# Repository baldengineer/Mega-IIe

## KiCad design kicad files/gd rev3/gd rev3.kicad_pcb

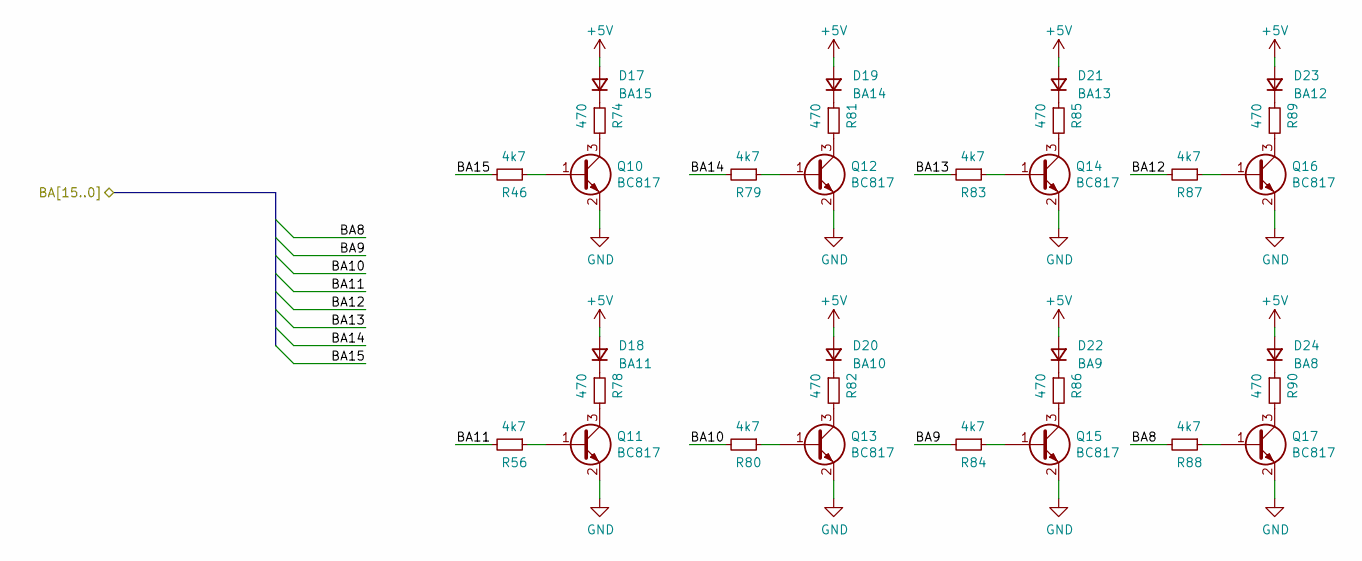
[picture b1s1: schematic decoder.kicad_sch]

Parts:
D17: BA15; LED_1206_3216Metric
D18: BA11; LED_1206_3216Metric
D19: BA14; LED_1206_3216Metric
D20: BA10; LED_1206_3216Metric
D21: BA13; LED_1206_3216Metric
D22: BA9; LED_1206_3216Metric
D23: BA12; LED_1206_3216Metric
D24: BA8; LED_1206_3216Metric
Q10, Q11, Q12, Q13, Q14, Q15, Q16, Q17: BC817; SOT-23
R46, R56, R79, R80, R83, R84, R87, R88: 4k7; R_0805_2012Metric
R74, R78, R81, R82, R85, R86, R89, R90: 470; R_0805_2012Metric

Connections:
/IWM/BA8: R88.2; also elsewhere on the board
/IWM/BA9: R84.2; also elsewhere on the board
/IWM/BA10: R80.2; also elsewhere on the board
/IWM/BA11: R56.2; also elsewhere on the board
/IWM/BA12: R87.2; also elsewhere on the board
/IWM/BA13: R83.2; also elsewhere on the board
/IWM/BA14: R79.2; also elsewhere on the board
/IWM/BA15: R46.2; also elsewhere on the board
GND: Q10.2 (E), Q11.2 (E), Q12.2 (E), Q13.2 (E), Q14.2 (E), Q15.2 (E), Q16.2 (E), Q17.2 (E); also elsewhere on the board
unnamed: D17.1 (K), R74.1
unnamed: D18.1 (K), R78.1
unnamed: D19.1 (K), R81.1
unnamed: D20.1 (K), R82.1
unnamed: D21.1 (K), R85.1
unnamed: D22.1 (K), R86.1
unnamed: D23.1 (K), R89.1
unnamed: D24.1 (K), R90.1
unnamed: Q10.1 (B), R46.1
unnamed: Q10.3 (C), R74.2
unnamed: Q11.1 (B), R56.1
unnamed: Q11.3 (C), R78.2
unnamed: Q12.1 (B), R79.1
unnamed: Q12.3 (C), R81.2
unnamed: Q13.1 (B), R80.1
unnamed: Q13.3 (C), R82.2
unnamed: Q14.1 (B), R83.1
unnamed: Q14.3 (C), R85.2
unnamed: Q15.1 (B), R84.1
unnamed: Q15.3 (C), R86.2
unnamed: Q16.1 (B), R87.1
unnamed: Q16.3 (C), R89.2
unnamed: Q17.1 (B), R88.1
unnamed: Q17.3 (C), R90.2

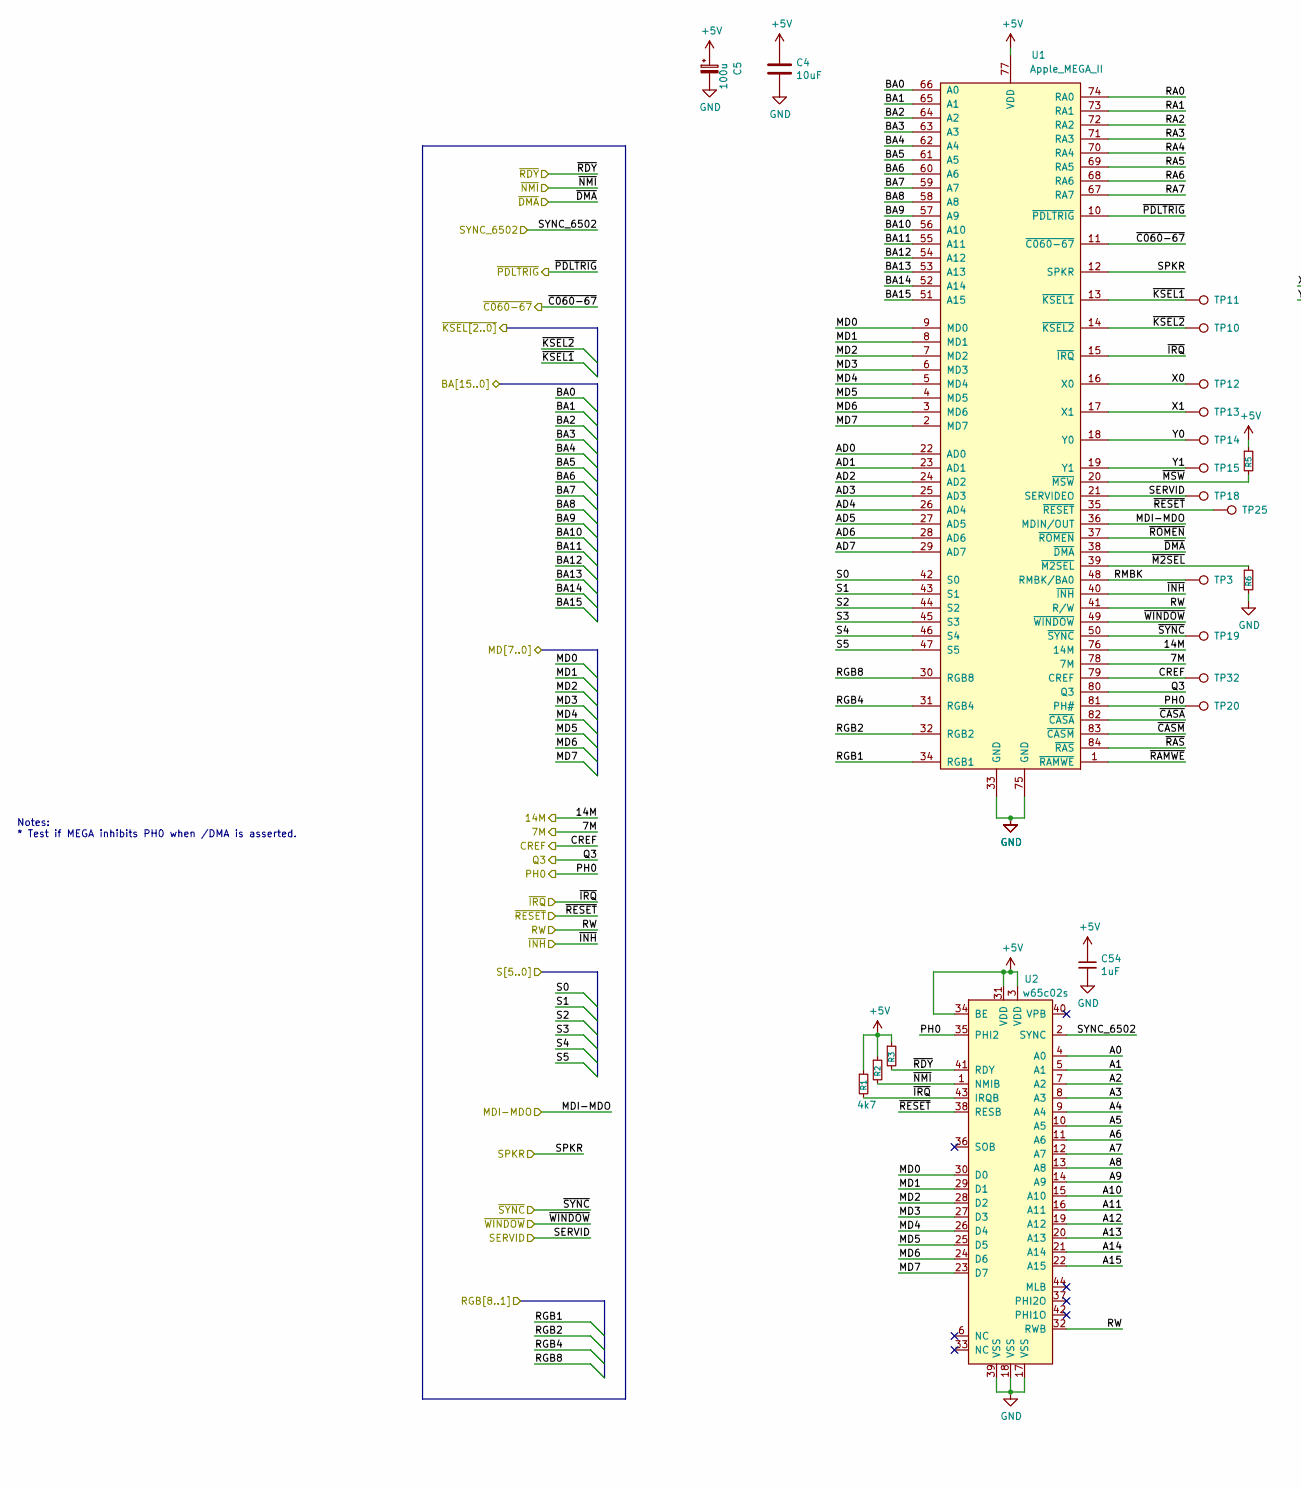
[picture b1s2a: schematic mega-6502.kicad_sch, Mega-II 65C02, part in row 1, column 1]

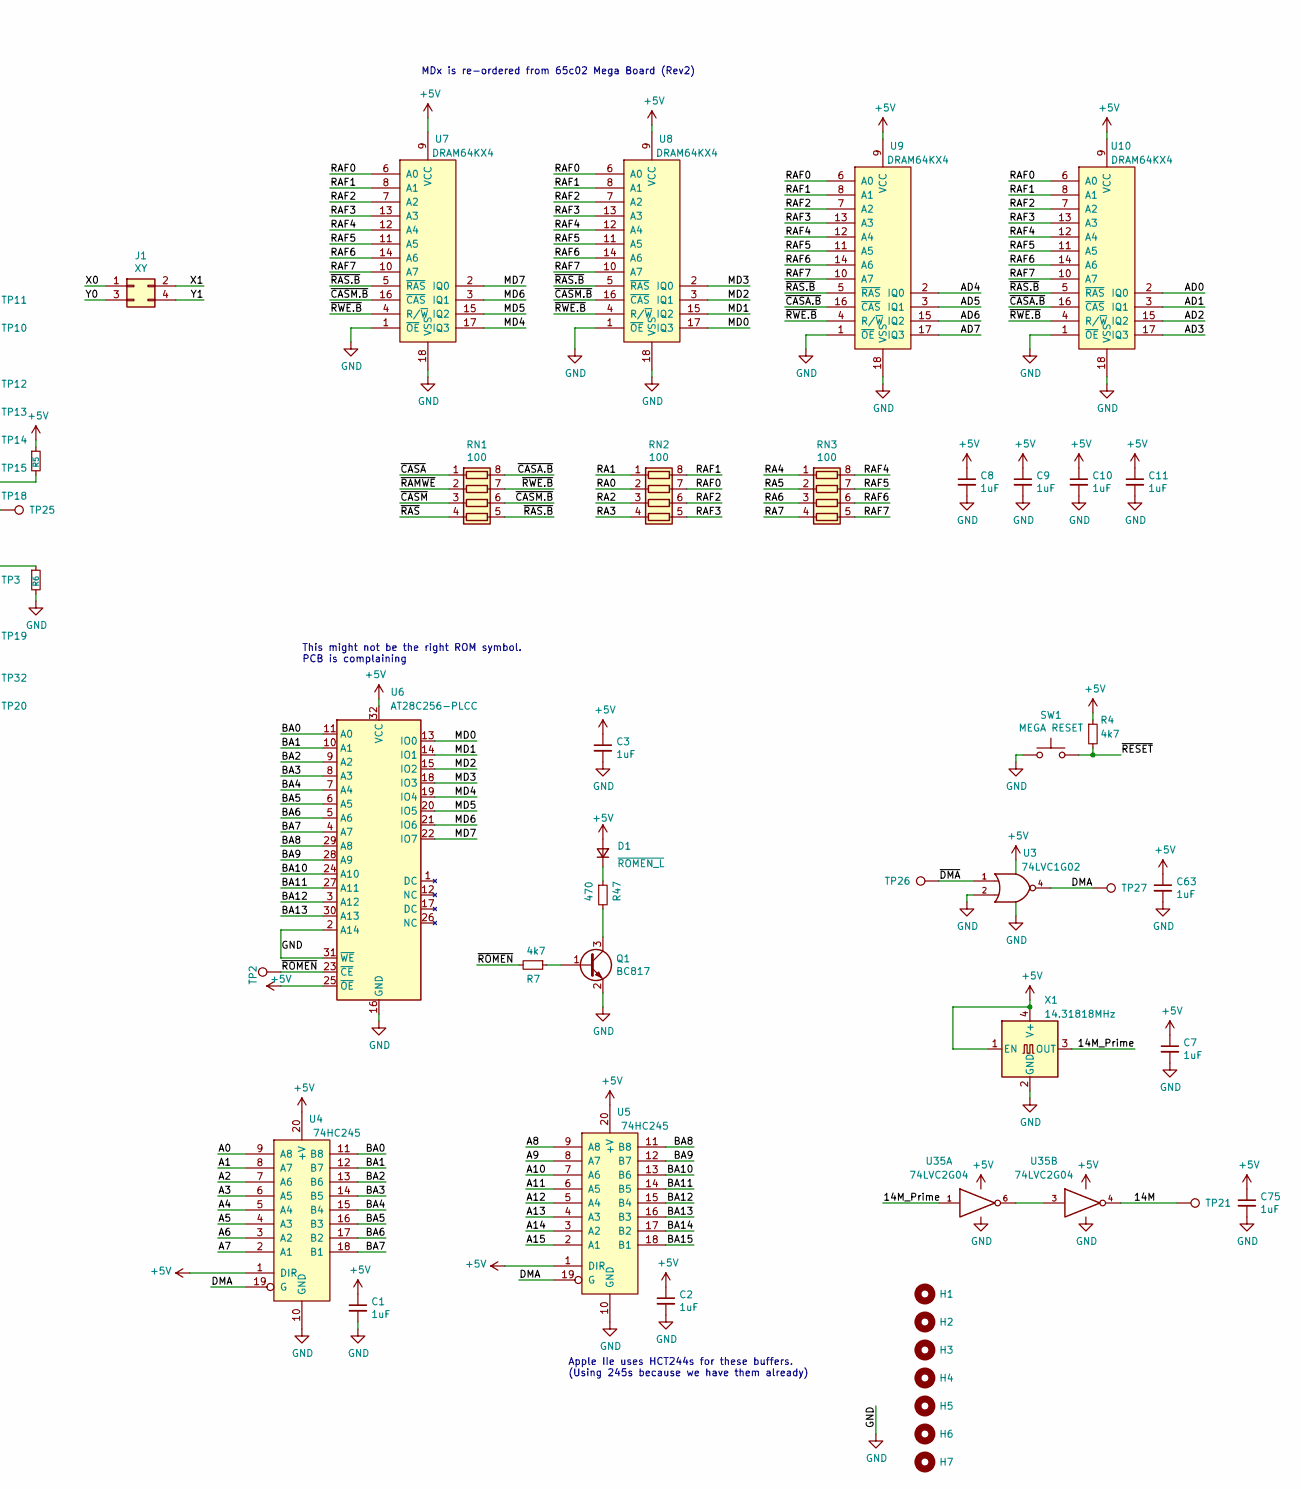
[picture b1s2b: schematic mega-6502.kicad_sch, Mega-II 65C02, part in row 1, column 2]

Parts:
C1, C2, C3, C7, C8, C9, C10, C11, C54, C63, C75: 1uF; C_0805_2012Metric
C4: 10uF; C_0805_2012Metric
C5: 100u; CP_EIA-3216-18_Kemet-A; MPN T520A107M006ATE035
D1: ~{ROMEN_L}; LED_1206_3216Metric
H1, H2, H3, H4, H5, H6, H7: MountingHole; MountingHole_2.5mm
J1: XY; PinHeader_2x02_P2.54mm_Vertical
Q1: BC817; SOT-23
R1: 4k7; R_0603_1608Metric
R2, R3: 3k3; R_0603_1608Metric
R4, R5, R6, R7: 4k7; R_0805_2012Metric
R47: 470; R_0805_2012Metric
RN1, RN2, RN3: 100; R_Array_Convex_4x0612
SW1: MEGA RESET; SW_SPST_PTS810
TP2: TestPoint_Harwin; TestPoint_Pad_D1.0mm
TP3, TP10, TP11, TP12, TP13, TP14, TP15, TP18, TP19, TP20, TP21, TP25, TP26, TP27, TP32: TestPoint; TestPoint_Pad_D1.0mm
U1: Apple_MEGA_II; PLCC-84_THT-Socket
U2: w65c02s; TQFP-44_10x10mm_P0.8mm
U3: 74LVC1G02; SOT-23-5
U4, U5: 74HC245; SO-20_5.3x12.6mm_P1.27mm
U6: AT28C256-PLCC; PLCC-32_11.4x14.0mm_P1.27mm
U7, U8, U9, U10: DRAM64KX4; DIP-18_W7.62mm_Socket_LongPads
U35: 74LVC2G04; SOT-23-6
X1: 14.31818MHz; Oscillator_SMD_EuroQuartz_XO91-4Pin_7.0x5.0mm; MPN MCSJK-6NC1-14.31818-25-B

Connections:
/Audio/SPKR: U1.12 (SPKR); also elsewhere on the board
/IWM/7M: U1.78 (7M); also elsewhere on the board
/IWM/BA0: U1.66 (A0), U4.11 (B8), U6.11 (A0); also elsewhere on the board
/IWM/BA1: U1.65 (A1), U4.12 (B7), U6.10 (A1); also elsewhere on the board
/IWM/BA2: U1.64 (A2), U4.13 (B6), U6.9 (A2); also elsewhere on the board
/IWM/BA3: U1.63 (A3), U4.14 (B5), U6.8 (A3); also elsewhere on the board
/IWM/BA4: U1.62 (A4), U4.15 (B4), U6.7 (A4); also elsewhere on the board
/IWM/BA5: U1.61 (A5), U4.16 (B3), U6.6 (A5); also elsewhere on the board
/IWM/BA6: U1.60 (A6), U4.17 (B2), U6.5 (A6); also elsewhere on the board
/IWM/BA7: U1.59 (A7), U4.18 (B1), U6.4 (A7); also elsewhere on the board
/IWM/BA8: U1.58 (A8), U5.11 (B8), U6.29 (A8); also elsewhere on the board
/IWM/BA9: U1.57 (A9), U5.12 (B7), U6.28 (A9); also elsewhere on the board
/IWM/BA10: U1.56 (A10), U5.13 (B6), U6.24 (A10); also elsewhere on the board
/IWM/BA11: U1.55 (A11), U5.14 (B5), U6.27 (A11); also elsewhere on the board
/IWM/BA12: U1.54 (A12), U5.15 (B4), U6.3 (A12); also elsewhere on the board
/IWM/BA13: U1.53 (A13), U5.16 (B3), U6.30 (A13); also elsewhere on the board
/IWM/BA14: U1.52 (A14), U5.17 (B2); also elsewhere on the board
/IWM/BA15: U1.51 (A15), U5.18 (B1); also elsewhere on the board
/IWM/MD0: U1.9 (MD0), U2.30 (D0), U6.13 (IO0), U8.17 (IQ3); also elsewhere on the board
/IWM/MD1: U1.8 (MD1), U2.29 (D1), U6.14 (IO1), U8.15 (IQ2); also elsewhere on the board
/IWM/MD2: U1.7 (MD2), U2.28 (D2), U6.15 (IO2), U8.3 (IQ1); also elsewhere on the board
/IWM/MD3: U1.6 (MD3), U2.27 (D3), U6.18 (IO3), U8.2 (IQ0); also elsewhere on the board
/IWM/MD4: U1.5 (MD4), U2.26 (D4), U6.19 (IO4), U7.17 (IQ3); also elsewhere on the board
/IWM/MD5: U1.4 (MD5), U2.25 (D5), U6.20 (IO5), U7.15 (IQ2); also elsewhere on the board
/IWM/MD6: U1.3 (MD6), U2.24 (D6), U6.21 (IO6), U7.3 (IQ1); also elsewhere on the board
/IWM/MD7: U1.2 (MD7), U2.23 (D7), U6.22 (IO7), U7.2 (IQ0); also elsewhere on the board
/IWM/Q3: U1.80 (Q3); also elsewhere on the board
/IWM/~RESET: R4.2, SW1.2, TP25.1, U1.35 (~RESET), U2.38 (RESB); also elsewhere on the board
/Slot/MDI-MDO: U1.36 (MDIN/OUT); also elsewhere on the board
/Slot/PH0: TP20.1, U1.81 (PH#), U2.35 (PHI2); also elsewhere on the board
/Slot/RW: U1.41 (R/W), U2.32 (RWB); also elsewhere on the board
/Slot/S0: U1.42 (S0); also elsewhere on the board
/Slot/S1: U1.43 (S1); also elsewhere on the board
/Slot/S2: U1.44 (S2); also elsewhere on the board
/Slot/S3: U1.45 (S3); also elsewhere on the board
/Slot/S4: U1.46 (S4); also elsewhere on the board
/Slot/S5: U1.47 (S5); also elsewhere on the board
/Slot/SYNC_6502: U2.2 (SYNC); also elsewhere on the board
/Slot/~DMA: TP26.1, U1.38 (~DMA), U3.1; also elsewhere on the board
/Slot/~INH: U1.40 (~INH); also elsewhere on the board
/Slot/~IRQ: R1.2, U1.15 (~IRQ), U2.43 (IRQB); also elsewhere on the board
/Slot/~NMI: R2.2, U2.1 (NMIB); also elsewhere on the board
/Slot/~RDY: R3.2, U2.41 (RDY); also elsewhere on the board
/game_port/~C060-67: U1.11 (~C060-67); also elsewhere on the board
/game_port/~PDLTRIG: U1.10 (~PDLTRIG); also elsewhere on the board
/mega-6502/14M: TP21.1, U1.76 (14M), U35.4; also elsewhere on the board
/mega-6502/14M_Prime: U35.1, X1.3 (OUT)
/mega-6502/A0: U2.4 (A0), U4.9 (A8)
/mega-6502/A1: U2.5 (A1), U4.8 (A7)
/mega-6502/A2: U2.7 (A2), U4.7 (A6)
/mega-6502/A3: U2.8 (A3), U4.6 (A5)
/mega-6502/A4: U2.9 (A4), U4.5 (A4)
/mega-6502/A5: U2.10 (A5), U4.4 (A3)
/mega-6502/A6: U2.11 (A6), U4.3 (A2)
/mega-6502/A7: U2.12 (A7), U4.2 (A1)
/mega-6502/A8: U2.13 (A8), U5.9 (A8)
/mega-6502/A9: U2.14 (A9), U5.8 (A7)
/mega-6502/A10: U2.15 (A10), U5.7 (A6)
/mega-6502/A11: U2.16 (A11), U5.6 (A5)
/mega-6502/A12: U2.19 (A12), U5.5 (A4)
/mega-6502/A13: U2.20 (A13), U5.4 (A3)
/mega-6502/A14: U2.21 (A14), U5.3 (A2)
/mega-6502/A15: U2.22 (A15), U5.2 (A1)
/mega-6502/AD0: U1.22 (AD0), U10.2 (IQ0)
/mega-6502/AD1: U1.23 (AD1), U10.3 (IQ1)
/mega-6502/AD2: U1.24 (AD2), U10.15 (IQ2)
/mega-6502/AD3: U1.25 (AD3), U10.17 (IQ3)
/mega-6502/AD4: U1.26 (AD4), U9.2 (IQ0)
/mega-6502/AD5: U1.27 (AD5), U9.3 (IQ1)
/mega-6502/AD6: U1.28 (AD6), U9.15 (IQ2)
/mega-6502/AD7: U1.29 (AD7), U9.17 (IQ3)
/mega-6502/CREF: TP32.1, U1.79 (CREF)
/mega-6502/DMA: TP27.1, U3.4, U4.19 (G), U5.19 (G)
/mega-6502/RA0: RN2.2 (R2.1), U1.74 (RA0)
/mega-6502/RA1: RN2.1 (R1.1), U1.73 (RA1)
/mega-6502/RA2: RN2.3 (R3.1), U1.72 (RA2)
/mega-6502/RA3: RN2.4 (R4.1), U1.71 (RA3)
/mega-6502/RA4: RN3.1 (R1.1), U1.70 (RA4)
/mega-6502/RA5: RN3.2 (R2.1), U1.69 (RA5)
/mega-6502/RA6: RN3.3 (R3.1), U1.68 (RA6)
/mega-6502/RA7: RN3.4 (R4.1), U1.67 (RA7)
/mega-6502/RAF0: RN2.7 (R2.2), U7.6 (A0), U8.6 (A0), U9.6 (A0), U10.6 (A0)
/mega-6502/RAF1: RN2.8 (R1.2), U7.8 (A1), U8.8 (A1), U9.8 (A1), U10.8 (A1)
/mega-6502/RAF2: RN2.6 (R3.2), U7.7 (A2), U8.7 (A2), U9.7 (A2), U10.7 (A2)
/mega-6502/RAF3: RN2.5 (R4.2), U7.13 (A3), U8.13 (A3), U9.13 (A3), U10.13 (A3)
/mega-6502/RAF4: RN3.8 (R1.2), U7.12 (A4), U8.12 (A4), U9.12 (A4), U10.12 (A4)
/mega-6502/RAF5: RN3.7 (R2.2), U7.11 (A5), U8.11 (A5), U9.11 (A5), U10.11 (A5)
/mega-6502/RAF6: RN3.6 (R3.2), U7.14 (A6), U8.14 (A6), U9.14 (A6), U10.14 (A6)
/mega-6502/RAF7: RN3.5 (R4.2), U7.10 (A7), U8.10 (A7), U9.10 (A7), U10.10 (A7)
/mega-6502/RGB1: U1.34 (RGB1); also elsewhere on the board
/mega-6502/RGB2: U1.32 (RGB2); also elsewhere on the board
/mega-6502/RGB4: U1.31 (RGB4); also elsewhere on the board
/mega-6502/RGB8: U1.30 (RGB8); also elsewhere on the board
/mega-6502/RMBK: TP3.1, U1.48 (RMBK/BA0)
/mega-6502/SERVID: TP18.1, U1.21 (SERVIDEO)
/mega-6502/X0: J1.1, TP12.1, U1.16 (X0)
/mega-6502/X1: J1.2, TP13.1, U1.17 (X1)
/mega-6502/Y0: J1.3, TP14.1, U1.18 (Y0)
/mega-6502/Y1: J1.4, TP15.1, U1.19 (Y1)
/mega-6502/~CASA.B: RN1.8 (R1.2), U9.16 (~CAS), U10.16 (~CAS)
/mega-6502/~CASA: RN1.1 (R1.1), U1.82 (~CASA)
/mega-6502/~CASM.B: RN1.6 (R3.2), U7.16 (~CAS), U8.16 (~CAS)
/mega-6502/~CASM: RN1.3 (R3.1), U1.83 (~CASM)
/mega-6502/~KSEL1: TP11.1, U1.13 (~KSEL1); also elsewhere on the board
/mega-6502/~KSEL2: TP10.1, U1.14 (~KSEL2); also elsewhere on the board
/mega-6502/~M2SEL: R6.1, U1.39 (~M2SEL)
/mega-6502/~MSW: R5.2, U1.20 (~MSW)
/mega-6502/~RAMWE: RN1.2 (R2.1), U1.1 (~RAMWE)
/mega-6502/~RAS.B: RN1.5 (R4.2), U7.5 (~RAS), U8.5 (~RAS), U9.5 (~RAS), U10.5 (~RAS)
/mega-6502/~RAS: RN1.4 (R4.1), U1.84 (~RAS)
/mega-6502/~ROMEN: R7.2, TP2.1, U1.37 (~ROMEN), U6.23 (~CE)
/mega-6502/~RWE.B: RN1.7 (R2.2), U7.4 (R/~W), U8.4 (R/~W), U9.4 (R/~W), U10.4 (R/~W)
/mega-6502/~SYNC: TP19.1, U1.50 (~SYNC); also elsewhere on the board
/mega-6502/~WINDOW: U1.49 (~WINDOW); also elsewhere on the board
GND: C1.2, C2.2, C3.2, C4.2, C5.2, C7.2, C8.2, C9.2, C10.2, C11.2, C54.2, C63.2, C75.2, Q1.2 (E), R6.2, SW1.1, U1.33 (GND), U1.75 (GND), U2.17 (VSS), U2.18 (VSS), U2.39 (VSS), U3.2, U3.3 (GND), U4.10 (GND), U5.10 (GND), U6.2 (A14), U6.16 (GND), U6.31 (~WE), U7.1 (~OE), U7.18 (VSS), U8.1 (~OE), U8.18 (VSS), U9.1 (~OE), U9.18 (VSS), U10.1 (~OE), U10.18 (VSS), U35.2 (GND), X1.2 (GND); also elsewhere on the board
unnamed: D1.1 (K), R47.1
unnamed: Q1.1 (B), R7.1
unnamed: Q1.3 (C), R47.2
unnamed: U35.3, U35.6

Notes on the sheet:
MDx is re-ordered from 65c02 Mega Board (Rev2)
Apple IIe uses HCT244s for these buffers. (Using 245s because we have them already)
This might not be the right ROM symbol. PCB is complaining
Notes: * Test if MEGA inhibits PH0 when /DMA is asserted.

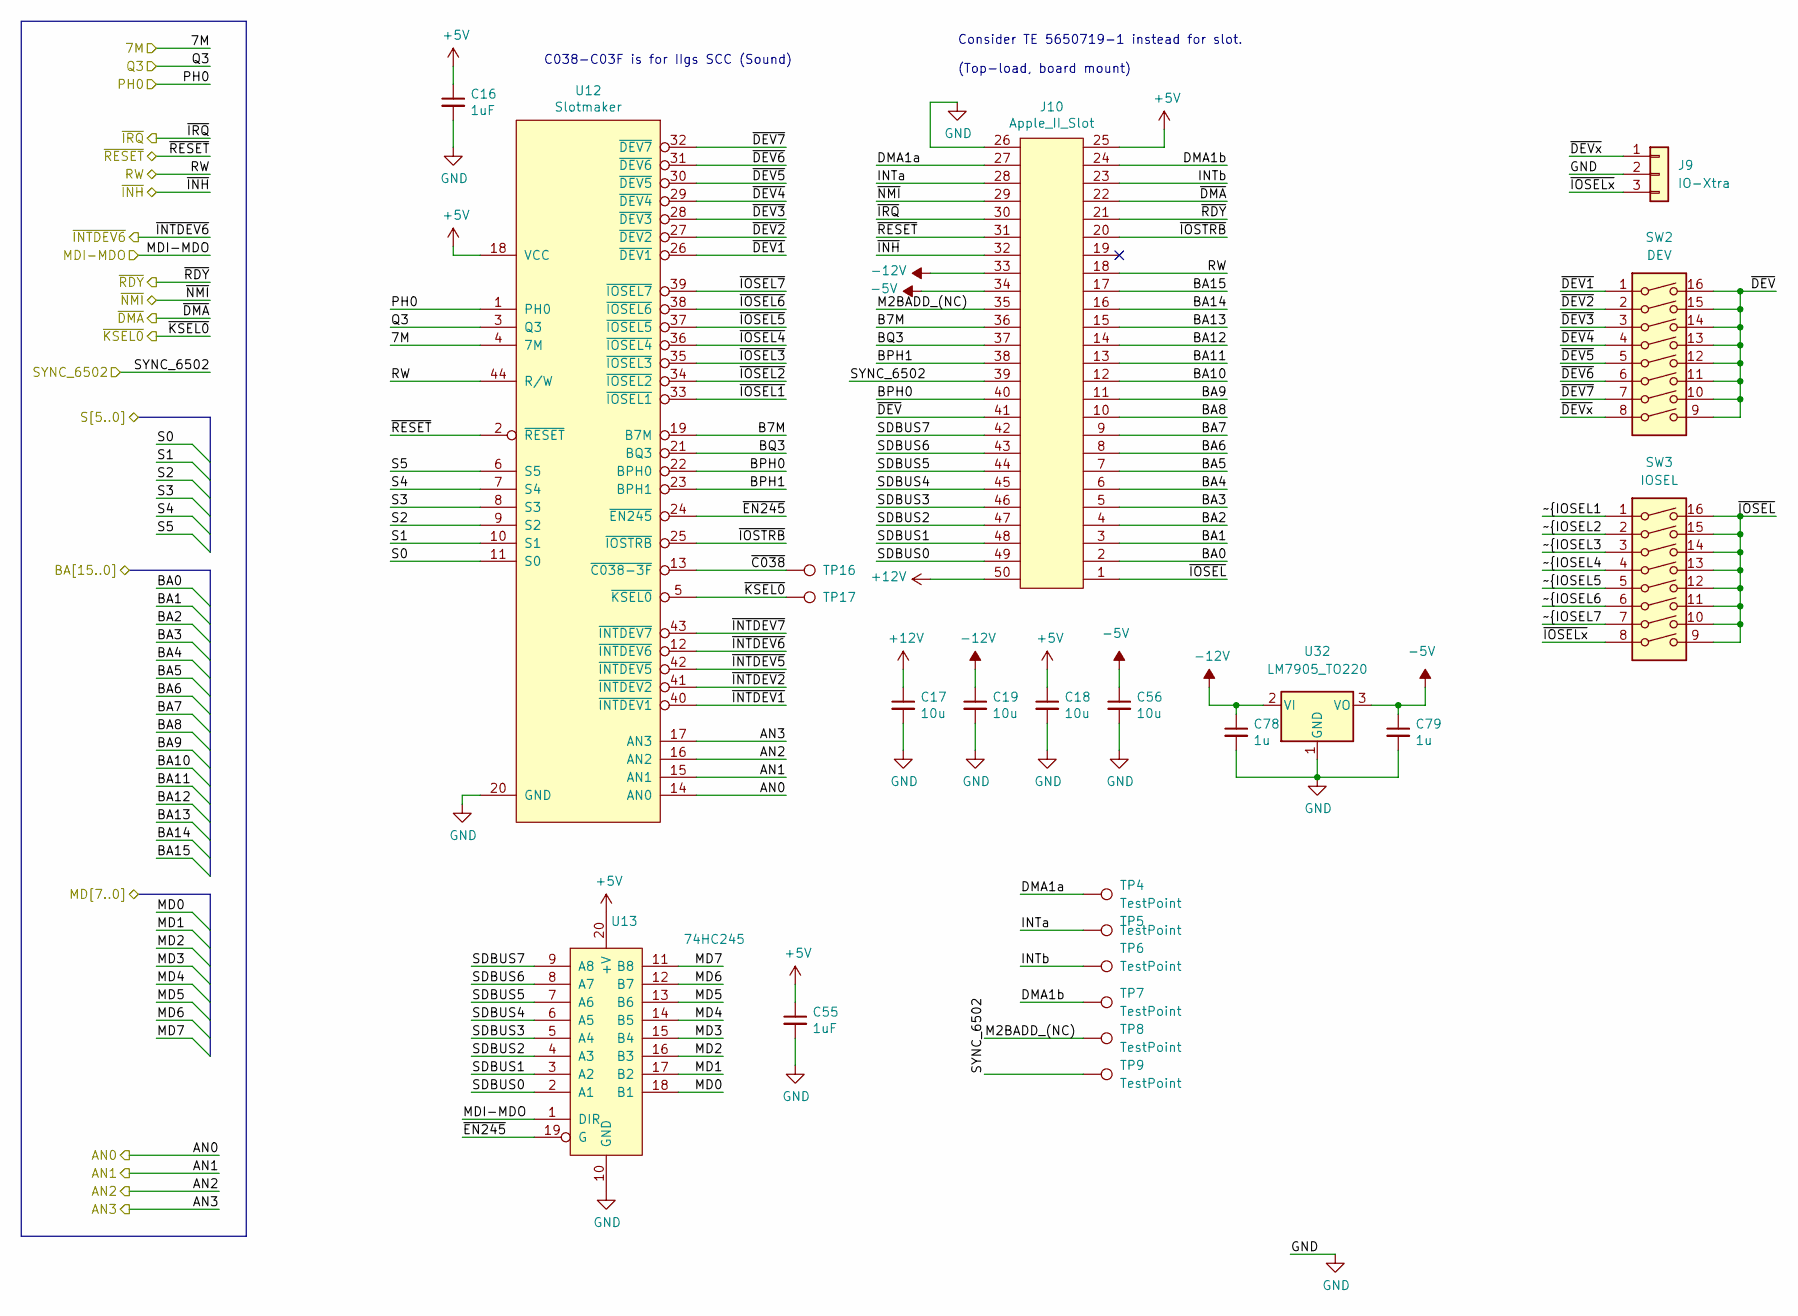
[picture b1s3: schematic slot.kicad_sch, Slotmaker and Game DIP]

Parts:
C16, C55: 1uF; C_0805_2012Metric
C17, C18, C19, C56: 10u; C_0805_2012Metric
C78, C79: 1u; C_0603_1608Metric
J9: IO-Xtra; PinHeader_1x03_P2.54mm_Vertical
J10: Apple_II_Slot; Sullins-EBC25DCWN-Edge Socket 50 pos (25x2) 0.100
SW2: DEV; SW_DIP_SPSTx08_Slide_Omron_A6H-8101_W6.15mm_P1.27mm
SW3: IOSEL; SW_DIP_SPSTx08_Slide_Omron_A6H-8101_W6.15mm_P1.27mm
TP4, TP5, TP6, TP7, TP8, TP9, TP16, TP17: TestPoint; TestPoint_Pad_D1.0mm
U12: Slotmaker; PLCC-44_THT-Socket
U13: 74HC245; SO-20_5.3x12.6mm_P1.27mm
U32: LM7905_TO220; TO-220-3_Vertical

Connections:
+12V: C17.1, J10.50; also elsewhere on the board
-5V: C56.1, C79.1, J10.34, U32.3 (VO)
-12V: C19.1, C78.1, J10.33, U32.2 (VI); also elsewhere on the board
/IWM/7M: U12.4 (7M); also elsewhere on the board
/IWM/BA0: J10.2; also elsewhere on the board
/IWM/BA1: J10.3; also elsewhere on the board
/IWM/BA2: J10.4; also elsewhere on the board
/IWM/BA3: J10.5; also elsewhere on the board
/IWM/BA4: J10.6; also elsewhere on the board
/IWM/BA5: J10.7; also elsewhere on the board
/IWM/BA6: J10.8; also elsewhere on the board
/IWM/BA7: J10.9; also elsewhere on the board
/IWM/BA8: J10.10; also elsewhere on the board
/IWM/BA9: J10.11; also elsewhere on the board
/IWM/BA10: J10.12; also elsewhere on the board
/IWM/BA11: J10.13; also elsewhere on the board
/IWM/BA12: J10.14; also elsewhere on the board
/IWM/BA13: J10.15; also elsewhere on the board
/IWM/BA14: J10.16; also elsewhere on the board
/IWM/BA15: J10.17; also elsewhere on the board
/IWM/MD0: U13.18 (B1); also elsewhere on the board
/IWM/MD1: U13.17 (B2); also elsewhere on the board
/IWM/MD2: U13.16 (B3); also elsewhere on the board
/IWM/MD3: U13.15 (B4); also elsewhere on the board
/IWM/MD4: U13.14 (B5); also elsewhere on the board
/IWM/MD5: U13.13 (B6); also elsewhere on the board
/IWM/MD6: U13.12 (B7); also elsewhere on the board
/IWM/MD7: U13.11 (B8); also elsewhere on the board
/IWM/Q3: U12.3 (Q3); also elsewhere on the board
/IWM/~INTDEV6: U12.12 (~INTDEV6); also elsewhere on the board
/IWM/~RESET: J10.31, U12.2 (~RESET); also elsewhere on the board
/Slot/AN0: U12.14 (AN0); also elsewhere on the board
/Slot/AN1: U12.15 (AN1); also elsewhere on the board
/Slot/AN2: U12.16 (AN2); also elsewhere on the board
/Slot/AN3: U12.17 (AN3); also elsewhere on the board
/Slot/B7M: J10.36, U12.19 (B7M)
/Slot/BPH0: J10.40, U12.22 (BPH0)
/Slot/BPH1: J10.38, U12.23 (BPH1)
/Slot/BQ3: J10.37, U12.21 (BQ3)
/Slot/DMA1a: J10.27, TP4.1
/Slot/DMA1b: J10.24, TP7.1
/Slot/INTa: J10.28, TP5.1
/Slot/INTb: J10.23, TP6.1
/Slot/M2BADD_(NC): J10.35, TP8.1
/Slot/MDI-MDO: U13.1 (DIR); also elsewhere on the board
/Slot/PH0: U12.1 (PH0); also elsewhere on the board
/Slot/RW: J10.18, U12.44 (R/W); also elsewhere on the board
/Slot/S0: U12.11 (S0); also elsewhere on the board
/Slot/S1: U12.10 (S1); also elsewhere on the board
/Slot/S2: U12.9 (S2); also elsewhere on the board
/Slot/S3: U12.8 (S3); also elsewhere on the board
/Slot/S4: U12.7 (S4); also elsewhere on the board
/Slot/S5: U12.6 (S5); also elsewhere on the board
/Slot/SDBUS0: J10.49, U13.2 (A1)
/Slot/SDBUS1: J10.48, U13.3 (A2)
/Slot/SDBUS2: J10.47, U13.4 (A3)
/Slot/SDBUS3: J10.46, U13.5 (A4)
/Slot/SDBUS4: J10.45, U13.6 (A5)
/Slot/SDBUS5: J10.44, U13.7 (A6)
/Slot/SDBUS6: J10.43, U13.8 (A7)
/Slot/SDBUS7: J10.42, U13.9 (A8)
/Slot/SYNC_6502: J10.39, TP9.1; also elsewhere on the board
/Slot/~C038: TP16.1, U12.13 (~C038-3F)
/Slot/~DEV1: SW2.1, U12.26 (~DEV1)
/Slot/~DEV2: SW2.2, U12.27 (~DEV2)
/Slot/~DEV3: SW2.3, U12.28 (~DEV3)
/Slot/~DEV4: SW2.4, U12.29 (~DEV4)
/Slot/~DEV5: SW2.5, U12.30 (~DEV5)
/Slot/~DEV6: SW2.6, U12.31 (~DEV6)
/Slot/~DEV7: SW2.7, U12.32 (~DEV7)
/Slot/~DEVx: J9.1, SW2.8
/Slot/~DEV: J10.41, SW2.9, SW2.10, SW2.11, SW2.12, SW2.13, SW2.14, SW2.15, SW2.16
/Slot/~DMA: J10.22; also elsewhere on the board
/Slot/~EN245: U12.24 (~EN245), U13.19 (G)
/Slot/~INH: J10.32; also elsewhere on the board
/Slot/~INTDEV1: U12.40 (~INTDEV1)
/Slot/~INTDEV2: U12.41 (~INTDEV2)
/Slot/~INTDEV5: U12.42 (~INTDEV5)
/Slot/~INTDEV7: U12.43 (~INTDEV7)
/Slot/~IOSELx: J9.3, SW3.8
/Slot/~IOSEL: J10.1, SW3.9, SW3.10, SW3.11, SW3.12, SW3.13, SW3.14, SW3.15, SW3.16
/Slot/~IOSTRB: J10.20, U12.25 (~IOSTRB)
/Slot/~IRQ: J10.30; also elsewhere on the board
/Slot/~NMI: J10.29; also elsewhere on the board
/Slot/~RDY: J10.21; also elsewhere on the board
/mega-6502/~KSEL0: TP17.1, U12.5 (~KSEL0); also elsewhere on the board
GND: C16.2, C17.2, C18.2, C19.2, C55.2, C56.2, C78.2, C79.2, J9.2, J10.26, U12.20 (GND), U13.10 (GND), U32.1 (GND); also elsewhere on the board

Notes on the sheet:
Consider TE 5650719-1 instead for slot. (Top-load, board mount)
C038-C03F is for IIgs SCC (Sound)
~{}

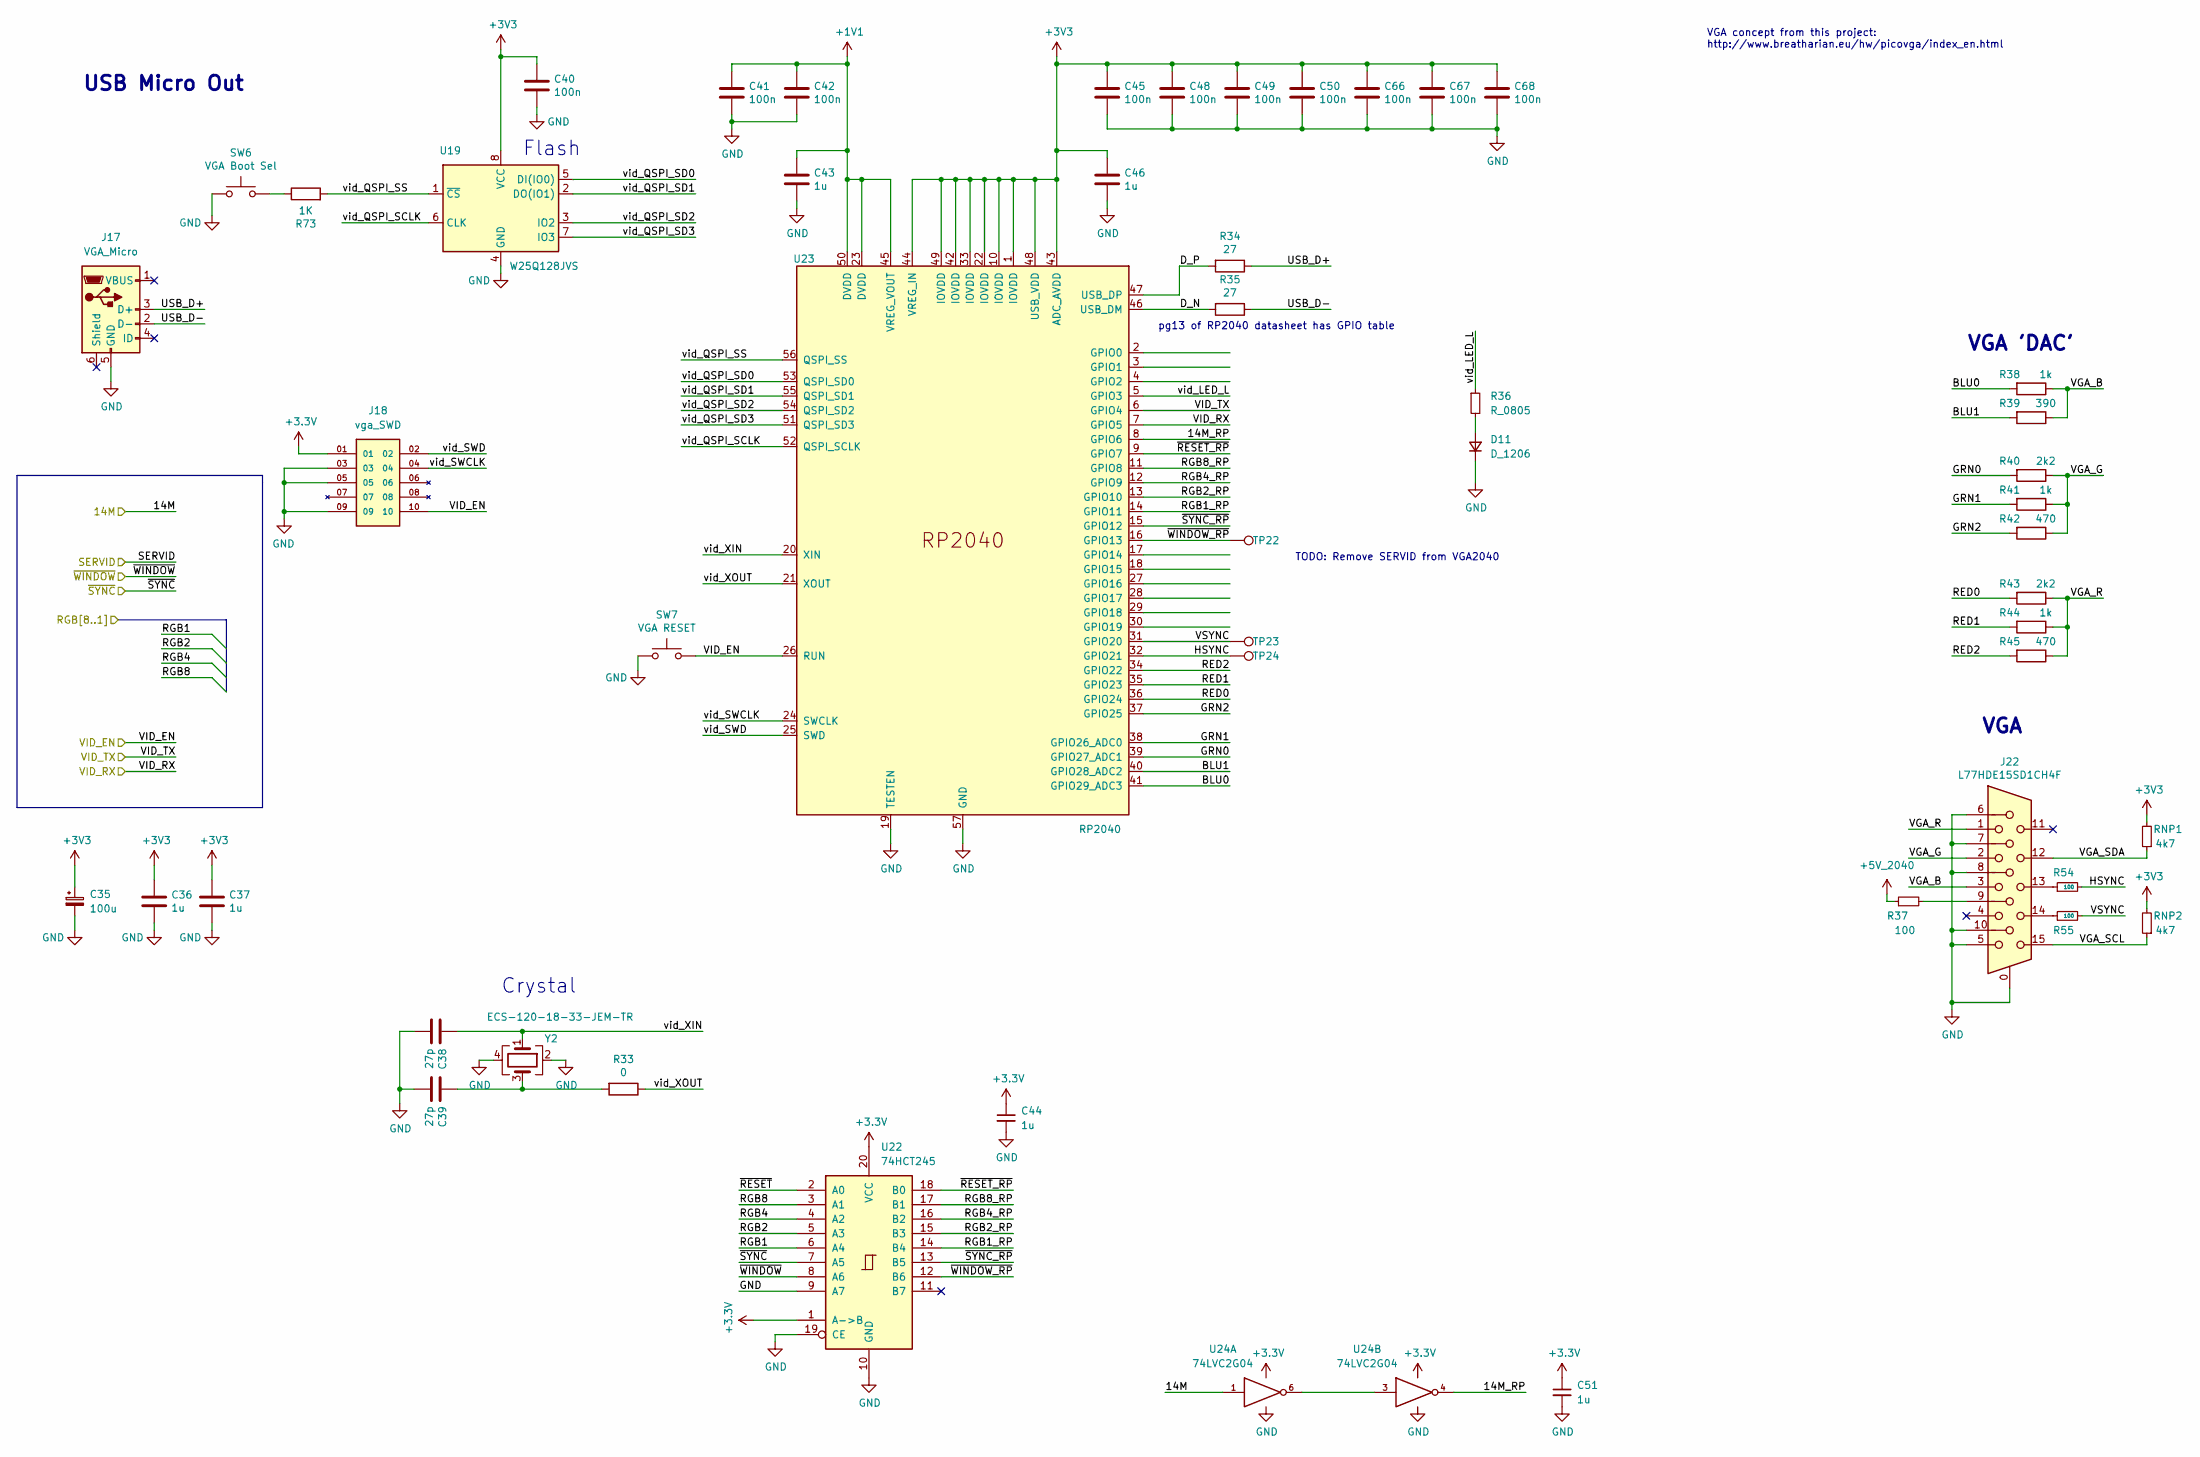
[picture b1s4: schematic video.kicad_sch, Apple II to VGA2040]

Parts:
C35: 100u; CP_EIA-3216-18_Kemet-A; MPN T520A107M006ATE035
C36, C37, C44, C51: 1u; C_0805_2012Metric
C38, C39: 27p; C_0603_1608Metric
C40: 100n; C_0805_2012Metric
C41, C42, C45, C48, C49, C50, C66, C67, C68: 100n; C_0603_1608Metric
C43, C46: 1u; C_0603_1608Metric
D11: D_1206; LED_1206_3216Metric
J17: VGA_Micro; USB_Micro-B_GCT_USB3076-30-A
J18: vga_SWD; SAMTEC_FTSH-105-XX-X-DV; PARTREV H
J22: L77HDE15SD1CH4F; DSUB-15-HD_Female_Horizontal_P2.29x1.98mm_EdgePinOffset8.35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
R33: 0; R_0603_1608Metric
R34, R35: 27; R_0603_1608Metric
R36: R_0805; R_0805_2012Metric
R37, R54, R55: 100; R_0805_2012Metric
R38, R41, R44: 1k; R_0402_1005Metric
R39: 390; R_0402_1005Metric
R40, R43: 2k2; R_0402_1005Metric
R42, R45: 470; R_0402_1005Metric
R73: 1K; R_0603_1608Metric
RNP1, RNP2: 4k7; R_0805_2012Metric
SW6: VGA Boot Sel; SW_SPST_PTS810
SW7: VGA RESET; SW_SPST_PTS810
TP22, TP23, TP24: TestPoint_Harwin; TestPoint_Pad_D1.0mm
U19: W25Q128JVS; SOIC-8_5.23x5.23mm_P1.27mm
U22: 74HCT245; SO-20_5.3x12.6mm_P1.27mm
U23: RP2040; RP2040-QFN-56
U24: 74LVC2G04; SOT-23-6
Y2: ECS-120-18-33-JEM-TR; Crystal_SMD_3225-4Pin_3.2x2.5mm

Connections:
+1V1: C41.1, C42.1, C43.1, U23.23 (DVDD), U23.45 (VREG_VOUT), U23.50 (DVDD); also elsewhere on the board
/mega-6502/14M: U24.1; also elsewhere on the board
/mega-6502/RGB1: U22.6 (A4); also elsewhere on the board
/mega-6502/RGB2: U22.5 (A3); also elsewhere on the board
/mega-6502/RGB4: U22.4 (A2); also elsewhere on the board
/mega-6502/RGB8: U22.3 (A1); also elsewhere on the board
/mega-6502/~SYNC: U22.7 (A5); also elsewhere on the board
/mega-6502/~WINDOW: U22.8 (A6); also elsewhere on the board
/rp2040-keyboard/RX_2040: U23.6 (GPIO4); also elsewhere on the board
/rp2040-keyboard/TX_2040: U23.7 (GPIO5); also elsewhere on the board
/rp2040-keyboard/VID_EN: J18.10, SW7.2, U23.26 (RUN)
/video/14M_RP: U23.8 (GPIO6), U24.4
/video/BLU0: R38.2, U23.41 (GPIO29_ADC3)
/video/BLU1: R39.2, U23.40 (GPIO28_ADC2)
/video/D_N: R35.2, U23.46 (USB_DM)
/video/D_P: R34.2, U23.47 (USB_DP)
/video/GRN0: R40.2, U23.39 (GPIO27_ADC1)
/video/GRN1: R41.2, U23.38 (GPIO26_ADC0)
/video/GRN2: R42.2, U23.37 (GPIO25)
/video/HSYNC: R54.2, TP24.1, U23.32 (GPIO21)
/video/RED0: R43.2, U23.36 (GPIO24)
/video/RED1: R44.2, U23.35 (GPIO23)
/video/RED2: R45.2, U23.34 (GPIO22)
/video/RGB1_RP: U22.14 (B4), U23.14 (GPIO11)
/video/RGB2_RP: U22.15 (B3), U23.13 (GPIO10)
/video/RGB4_RP: U22.16 (B2), U23.12 (GPIO9)
/video/RGB8_RP: U22.17 (B1), U23.11 (GPIO8)
/video/USB_D+: J17.3 (D+), R34.1
/video/USB_D-: J17.2 (D-), R35.1
/video/VGA_B: J22.3, R38.1, R39.1
/video/VGA_G: J22.2, R40.1, R41.1, R42.1
/video/VGA_R: J22.1, R43.1, R44.1, R45.1
/video/VGA_SCL: J22.15, RNP2.1
/video/VGA_SDA: J22.12, RNP1.1
/video/VSYNC: R55.2, TP23.1, U23.31 (GPIO20)
/video/vid_LED_L: R36.1, U23.5 (GPIO3)
/video/vid_QSPI_SCLK: U19.6 (CLK), U23.52 (QSPI_SCLK)
/video/vid_QSPI_SD0: U19.5 (DI(IO0)), U23.53 (QSPI_SD0)
/video/vid_QSPI_SD1: U19.2 (DO(IO1)), U23.55 (QSPI_SD1)
/video/vid_QSPI_SD2: U19.3 (IO2), U23.54 (QSPI_SD2)
/video/vid_QSPI_SD3: U19.7 (IO3), U23.51 (QSPI_SD3)
/video/vid_QSPI_SS: R73.2, U19.1 (~CS), U23.56 (QSPI_SS)
/video/vid_SWCLK: J18.04, U23.24 (SWCLK)
/video/vid_SWD: J18.02, U23.25 (SWD)
/video/vid_XIN: C38.1, U23.20 (XIN), Y2.1
/video/vid_XOUT: R33.1, U23.21 (XOUT)
/video/~RESET_RP: U22.18 (B0), U23.9 (GPIO7)
/video/~RESET: U22.2 (A0)
/video/~SYNC_RP: U22.13 (B5), U23.15 (GPIO12)
/video/~WINDOW_RP: TP22.1, U22.12 (B6), U23.16 (GPIO13)
GND: C35.2, C36.2, C37.2, C38.2, C39.2, C40.2, C41.2, C42.2, C43.2, C44.2, C45.2, C46.2, C48.2, C49.2, C50.2, C51.2, C66.2, C67.2, C68.2, D11.1 (K), J17.5 (GND), J18.03, J18.05, J18.09, J22.0, J22.5, J22.6, J22.7, J22.8, J22.10, SW6.1, SW7.1, U19.4 (GND), U22.9 (A7), U22.10 (GND), U22.19 (CE), U23.19 (TESTEN), U23.57 (GND), U24.2 (GND), Y2.2, Y2.4; also elsewhere on the board
unnamed: C39.1, R33.2, Y2.3
unnamed: D11.2 (A), R36.2
unnamed: J22.9, R37.2
unnamed: J22.13, R54.1
unnamed: J22.14, R55.1
unnamed: R73.1, SW6.2
unnamed: U24.3, U24.6

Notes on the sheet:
Crystal
VGA
Flash
VGA concept from this project: http://www.breatharian.eu/hw/picovga/index_en.html
TODO: Remove SERVID from VGA2040
pg13 of RP2040 datasheet has GPIO table
VGA 'DAC'
USB Micro Out
